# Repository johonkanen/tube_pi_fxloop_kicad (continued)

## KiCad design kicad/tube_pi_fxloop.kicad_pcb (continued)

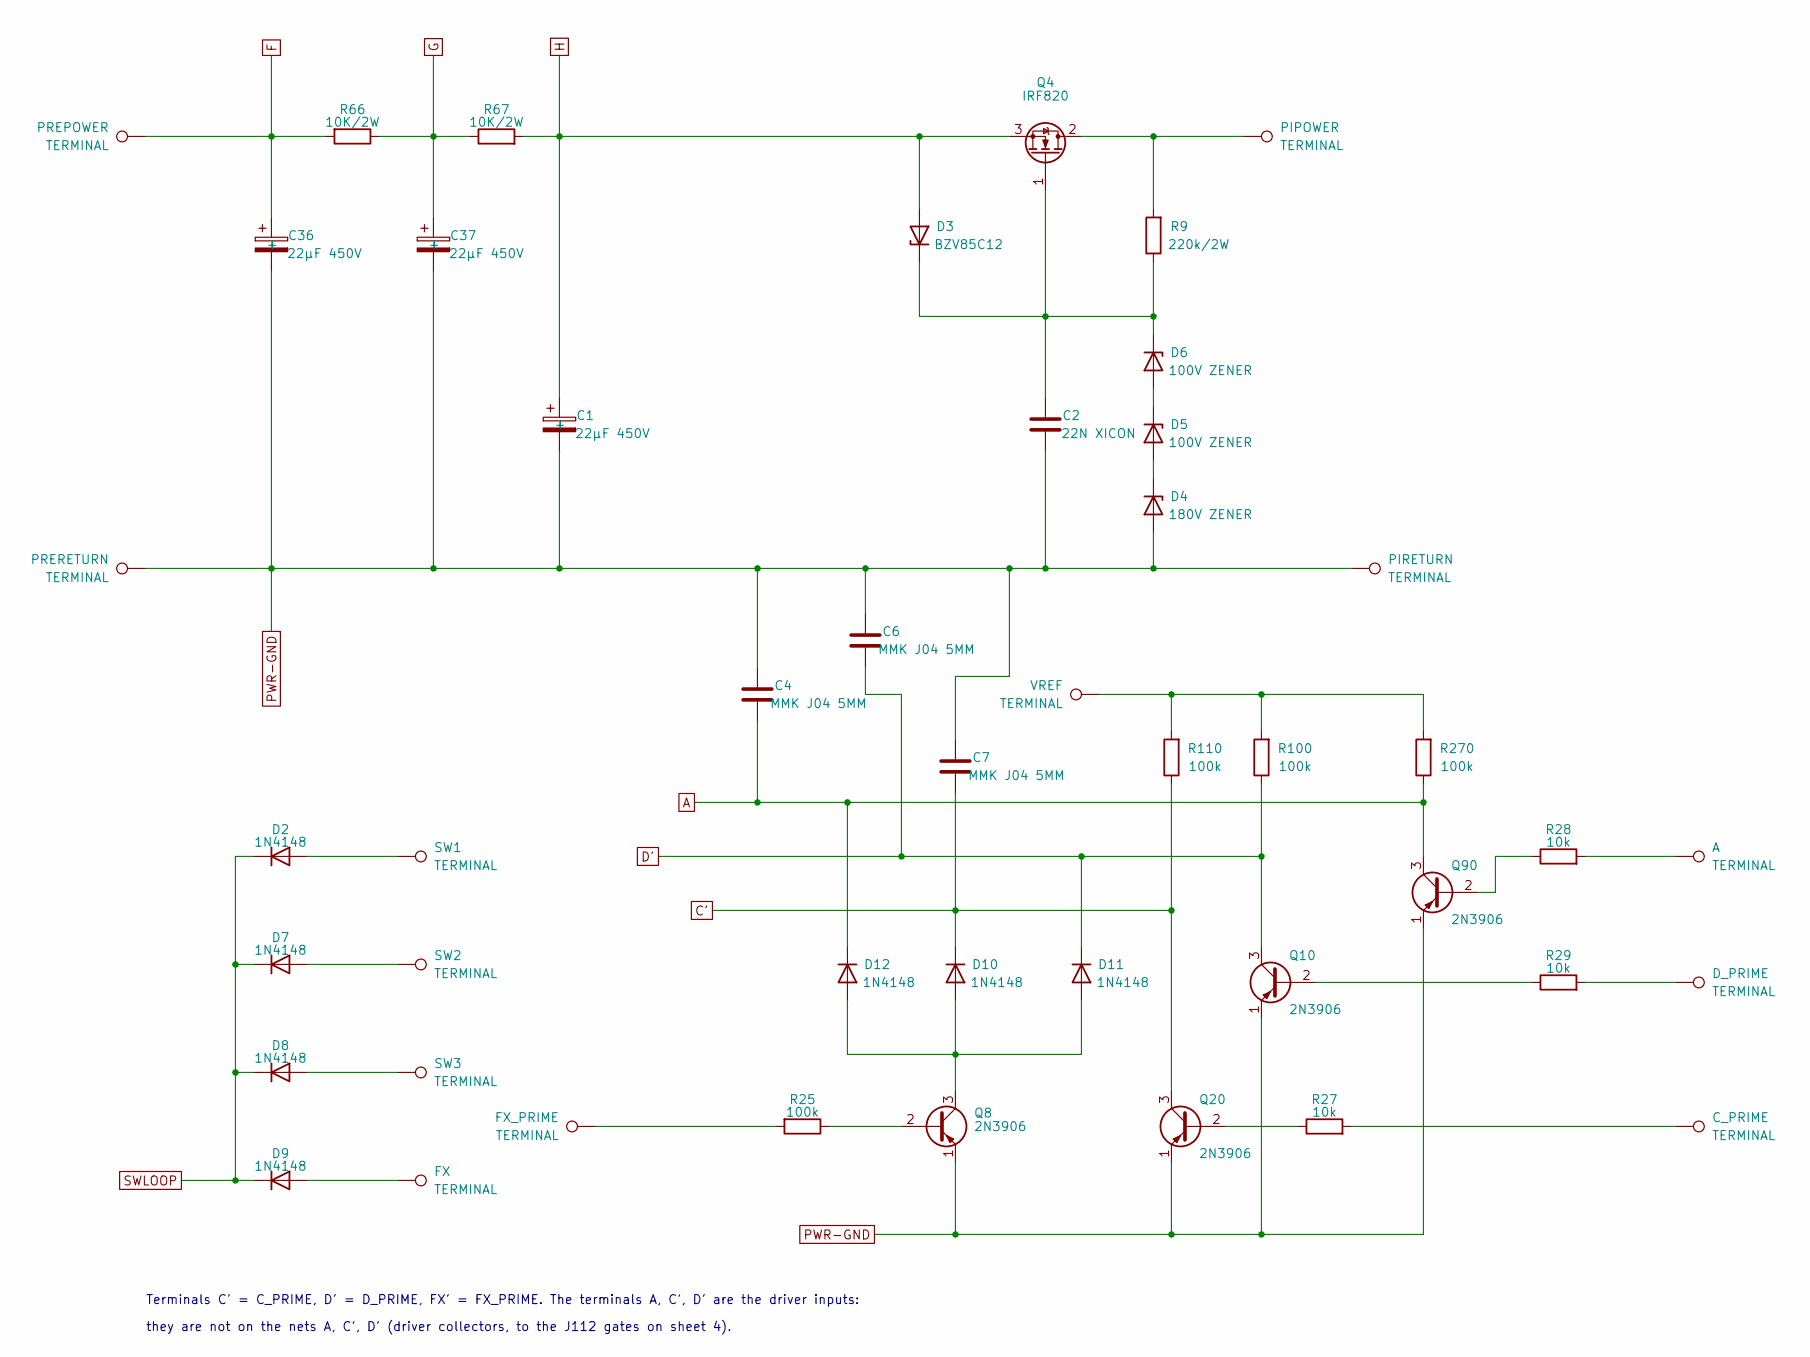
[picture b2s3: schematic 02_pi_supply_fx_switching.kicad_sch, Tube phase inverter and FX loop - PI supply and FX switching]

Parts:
A: TERMINAL; FlyLead_Pad_D3.048mm_Drill1.524mm
C1, C36, C37: 22µF 450V; CP_Radial_D16.0mm_P7.50mm_21
C2: 22N XICON; C_Rect_L13.0mm_W6.0mm_P9.70mm
C4, C6, C7: MMK J04 5MM; C_Rect_L7.2mm_W5.0mm_P5.00mm
C_PRIME: TERMINAL; FlyLead_Pad_D3.048mm_Drill1.524mm
D2, D7, D8, D9, D10, D11, D12: 1N4148; D_DO-35_SOD27_P10.16mm_Horizontal_AK
D3: BZV85C12; D_DO-41_SOD81_P10.16mm_Horizontal_AK
D4: 180V ZENER; D_DO-41_SOD81_P10.16mm_Horizontal_AK
D5, D6: 100V ZENER; D_DO-41_SOD81_P10.16mm_Horizontal_AK
D_PRIME: TERMINAL; FlyLead_Pad_D3.048mm_Drill1.524mm
FX: TERMINAL; FlyLead_Pad_D3.048mm_Drill1.524mm
FX_PRIME: TERMINAL; FlyLead_Pad_D3.048mm_Drill1.524mm
PIPOWER: TERMINAL; FlyLead_Pad_D3.048mm_Drill1.524mm
PIRETURN: TERMINAL; FlyLead_Pad_D3.048mm_Drill1.524mm
PREPOWER: TERMINAL; FlyLead_Pad_D3.048mm_Drill1.524mm
PRERETURN: TERMINAL; FlyLead_Pad_D3.048mm_Drill1.524mm
Q4: IRF820; TO-220-3_Vertical
Q8, Q10, Q20, Q90: 2N3906; TO-92_Inline_P2.03mm
R9: 220k/2W; R_Axial_DIN0414_L11.9mm_D4.5mm_P19.05mm_Horizontal
R25, R100, R110, R270: 100k; R_Axial_DIN0207_L6.3mm_D2.5mm_P10.16mm_Horizontal
R27, R28, R29: 10k; R_Axial_DIN0207_L6.3mm_D2.5mm_P10.16mm_Horizontal
R66, R67: 10K/2W; R_Axial_DIN0414_L11.9mm_D4.5mm_P19.05mm_Horizontal
SW1, SW2, SW3: TERMINAL; FlyLead_Pad_D3.048mm_Drill1.524mm
VREF: TERMINAL; FlyLead_Pad_D3.048mm_Drill1.524mm

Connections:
A: C4.2, D12.K, Q90.3 (C), R270.1; also elsewhere on the board
C': C7.2, D10.K, Q20.3 (C), R110.1; also elsewhere on the board
D': C6.2, D11.K, Q10.3 (C), R100.1; also elsewhere on the board
F: C36.2 (+), PREPOWER.1, R66.2; also elsewhere on the board
G: C37.2 (+), R66.1, R67.1; also elsewhere on the board
H: C1.2 (+), D3.A, Q4.3 (S), R67.2; also elsewhere on the board
unnamed: A.1, R28.2
unnamed: C_PRIME.1, R27.2
unnamed: D2.A, SW1.1
unnamed: D4.K, D5.A
unnamed: D5.K, D6.A
unnamed: D7.A, SW2.1
unnamed: D8.A, SW3.1
unnamed: D9.A, FX.1
unnamed: D_PRIME.1, R29.2
unnamed: FX_PRIME.1, R25.2
unnamed: PIPOWER.1, Q4.2 (D), R9.2
unnamed: C2.2, D3.K, D6.K, Q4.1 (G), R9.1
unnamed: Q8.2 (B), R25.1
unnamed: D10.A, D11.A, D12.A, Q8.3 (C)
unnamed: Q10.2 (B), R29.1
unnamed: Q20.2 (B), R27.1
unnamed: Q90.2 (B), R28.1
unnamed: R100.2, R110.2, R270.2, VREF.1
PWR-GND: C1.1 (-), C2.1, C4.1, C6.1, C7.1, C36.1 (-), C37.1 (-), D4.A, PIRETURN.1, PRERETURN.1, Q8.1 (E), Q10.1 (E), Q20.1 (E), Q90.1 (E); also elsewhere on the board
SWLOOP: D2.K, D7.K, D8.K, D9.K; also elsewhere on the board

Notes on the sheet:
Terminals C' = C_PRIME, D' = D_PRIME, FX' = FX_PRIME. The terminals A, C', D' are the driver inputs:
they are not on the nets A, C', D' (driver collectors, to the J112 gates on sheet 4).

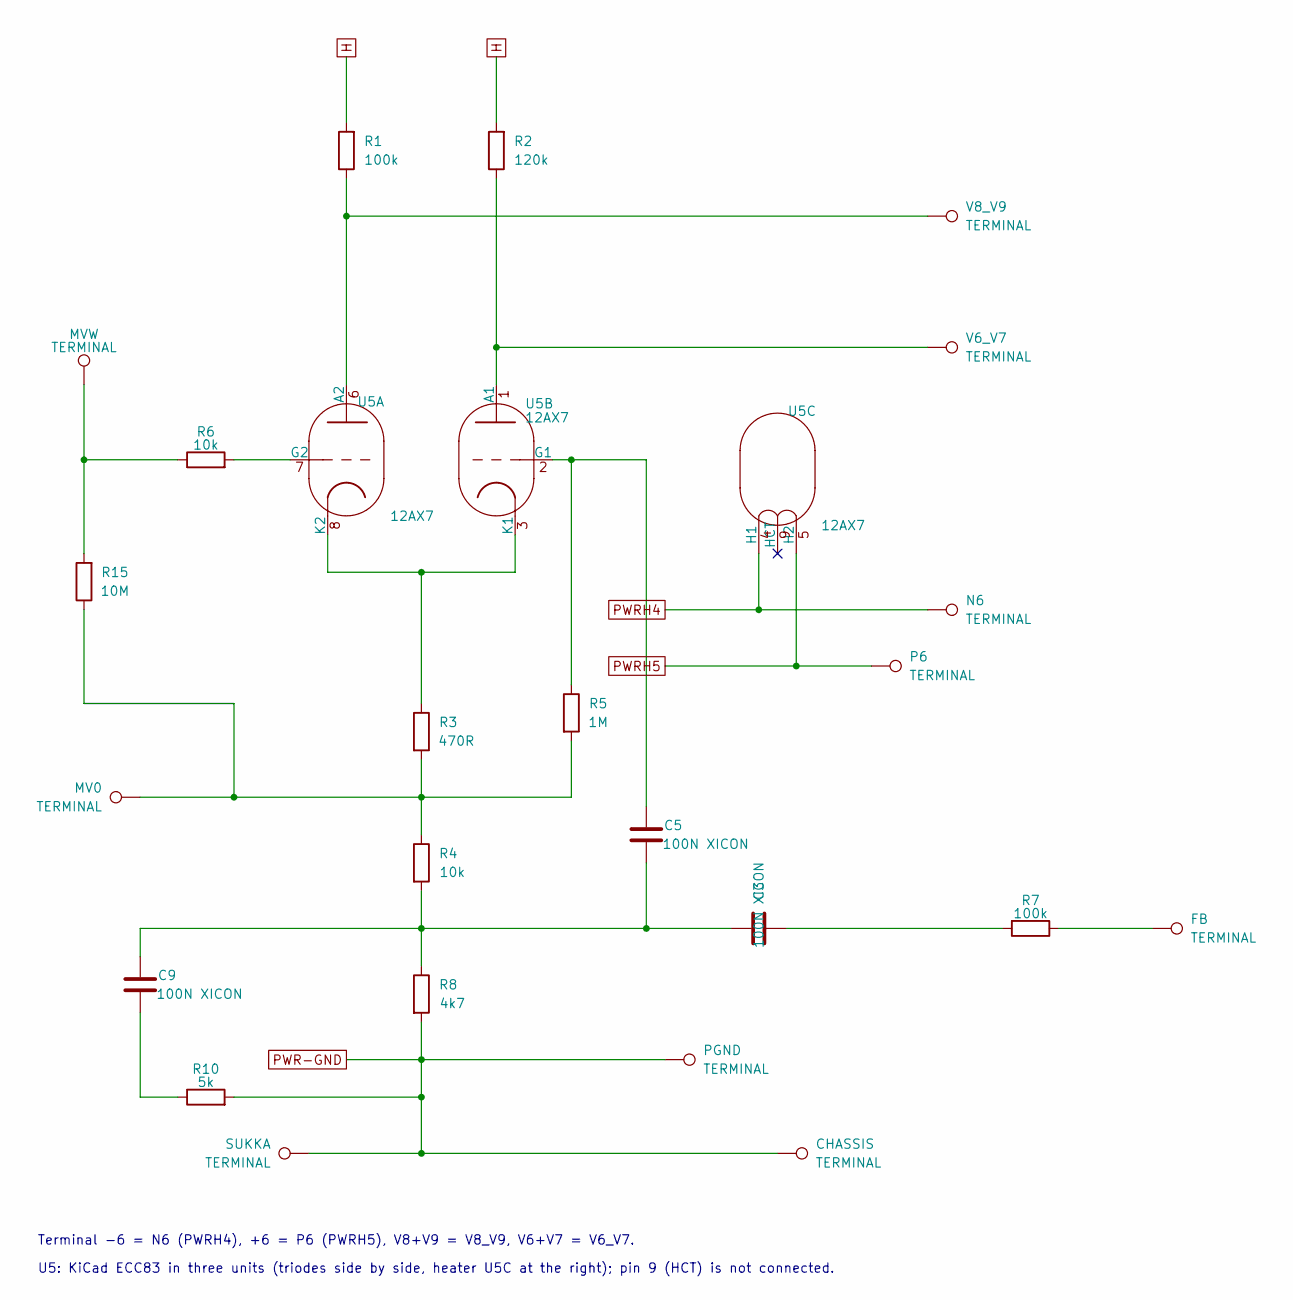
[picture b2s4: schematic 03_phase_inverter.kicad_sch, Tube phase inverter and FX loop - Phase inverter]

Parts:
C3, C5, C9: 100N XICON; C_Rect_L23.1mm_W6.0mm_P20.00mm
CHASSIS: TERMINAL; FlyLead_Pad_D3.048mm_Drill1.524mm
FB: TERMINAL; FlyLead_Pad_D3.048mm_Drill1.524mm
MV0: TERMINAL; FlyLead_Pad_D3.048mm_Drill1.524mm
MVW: TERMINAL; FlyLead_Pad_D3.048mm_Drill1.524mm
N6: TERMINAL; FlyLead_Pad_D3.048mm_Drill1.524mm
P6: TERMINAL; FlyLead_Pad_D3.048mm_Drill1.524mm
PGND: TERMINAL; FlyLead_Pad_D3.048mm_Drill1.524mm
R1: 100k; R_Axial_DIN0414_L11.9mm_D4.5mm_P19.05mm_Horizontal
R2: 120k; R_Axial_DIN0414_L11.9mm_D4.5mm_P19.05mm_Horizontal
R3: 470R; R_Axial_DIN0207_L6.3mm_D2.5mm_P10.16mm_Horizontal
R4, R6: 10k; R_Axial_DIN0207_L6.3mm_D2.5mm_P10.16mm_Horizontal
R5: 1M; R_Axial_DIN0207_L6.3mm_D2.5mm_P10.16mm_Horizontal
R7: 100k; R_Axial_DIN0207_L6.3mm_D2.5mm_P10.16mm_Horizontal
R8: 4k7; R_Axial_DIN0207_L6.3mm_D2.5mm_P10.16mm_Horizontal
R10: 5k; R_Axial_DIN0207_L6.3mm_D2.5mm_P10.16mm_Horizontal
R15: 10M; R_Axial_DIN0207_L6.3mm_D2.5mm_P10.16mm_Horizontal
SUKKA: TERMINAL; FlyLead_Pad_D3.048mm_Drill1.524mm
U5: 12AX7; Valve_Noval_Belton_PCD21.00mm
V6_V7, V8_V9: TERMINAL; FlyLead_Pad_D3.048mm_Drill1.524mm

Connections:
H: R1.2, R2.2; also elsewhere on the board
unnamed: C3.1, R7.2
unnamed: C3.2, C5.1, C9.2, R4.2, R8.1
unnamed: C9.1, R10.1
unnamed: FB.1, R7.1
unnamed: MV0.1, R3.2, R4.1, R5.2, R15.1
unnamed: MVW.1, R6.1, R15.2
unnamed: R1.1, U5.6 (A2), V8_V9.1
unnamed: R6.2, U5.7 (G2)
unnamed: R3.1, U5.3 (K1), U5.8 (K2)
unnamed: R2.1, U5.1 (A1), V6_V7.1
unnamed: C5.2, R5.1, U5.2 (G1)
PWR-GND: CHASSIS.1, PGND.1, R8.2, R10.2, SUKKA.1; also elsewhere on the board
PWRH4: N6.1, U5.4 (H1); also elsewhere on the board
PWRH5: P6.1, U5.5 (H2); also elsewhere on the board

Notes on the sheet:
Terminal -6 = N6 (PWRH4), +6 = P6 (PWRH5), V8+V9 = V8_V9, V6+V7 = V6_V7.
U5: KiCad ECC83 in three units (triodes side by side, heater U5C at the right); pin 9 (HCT) is not connected.

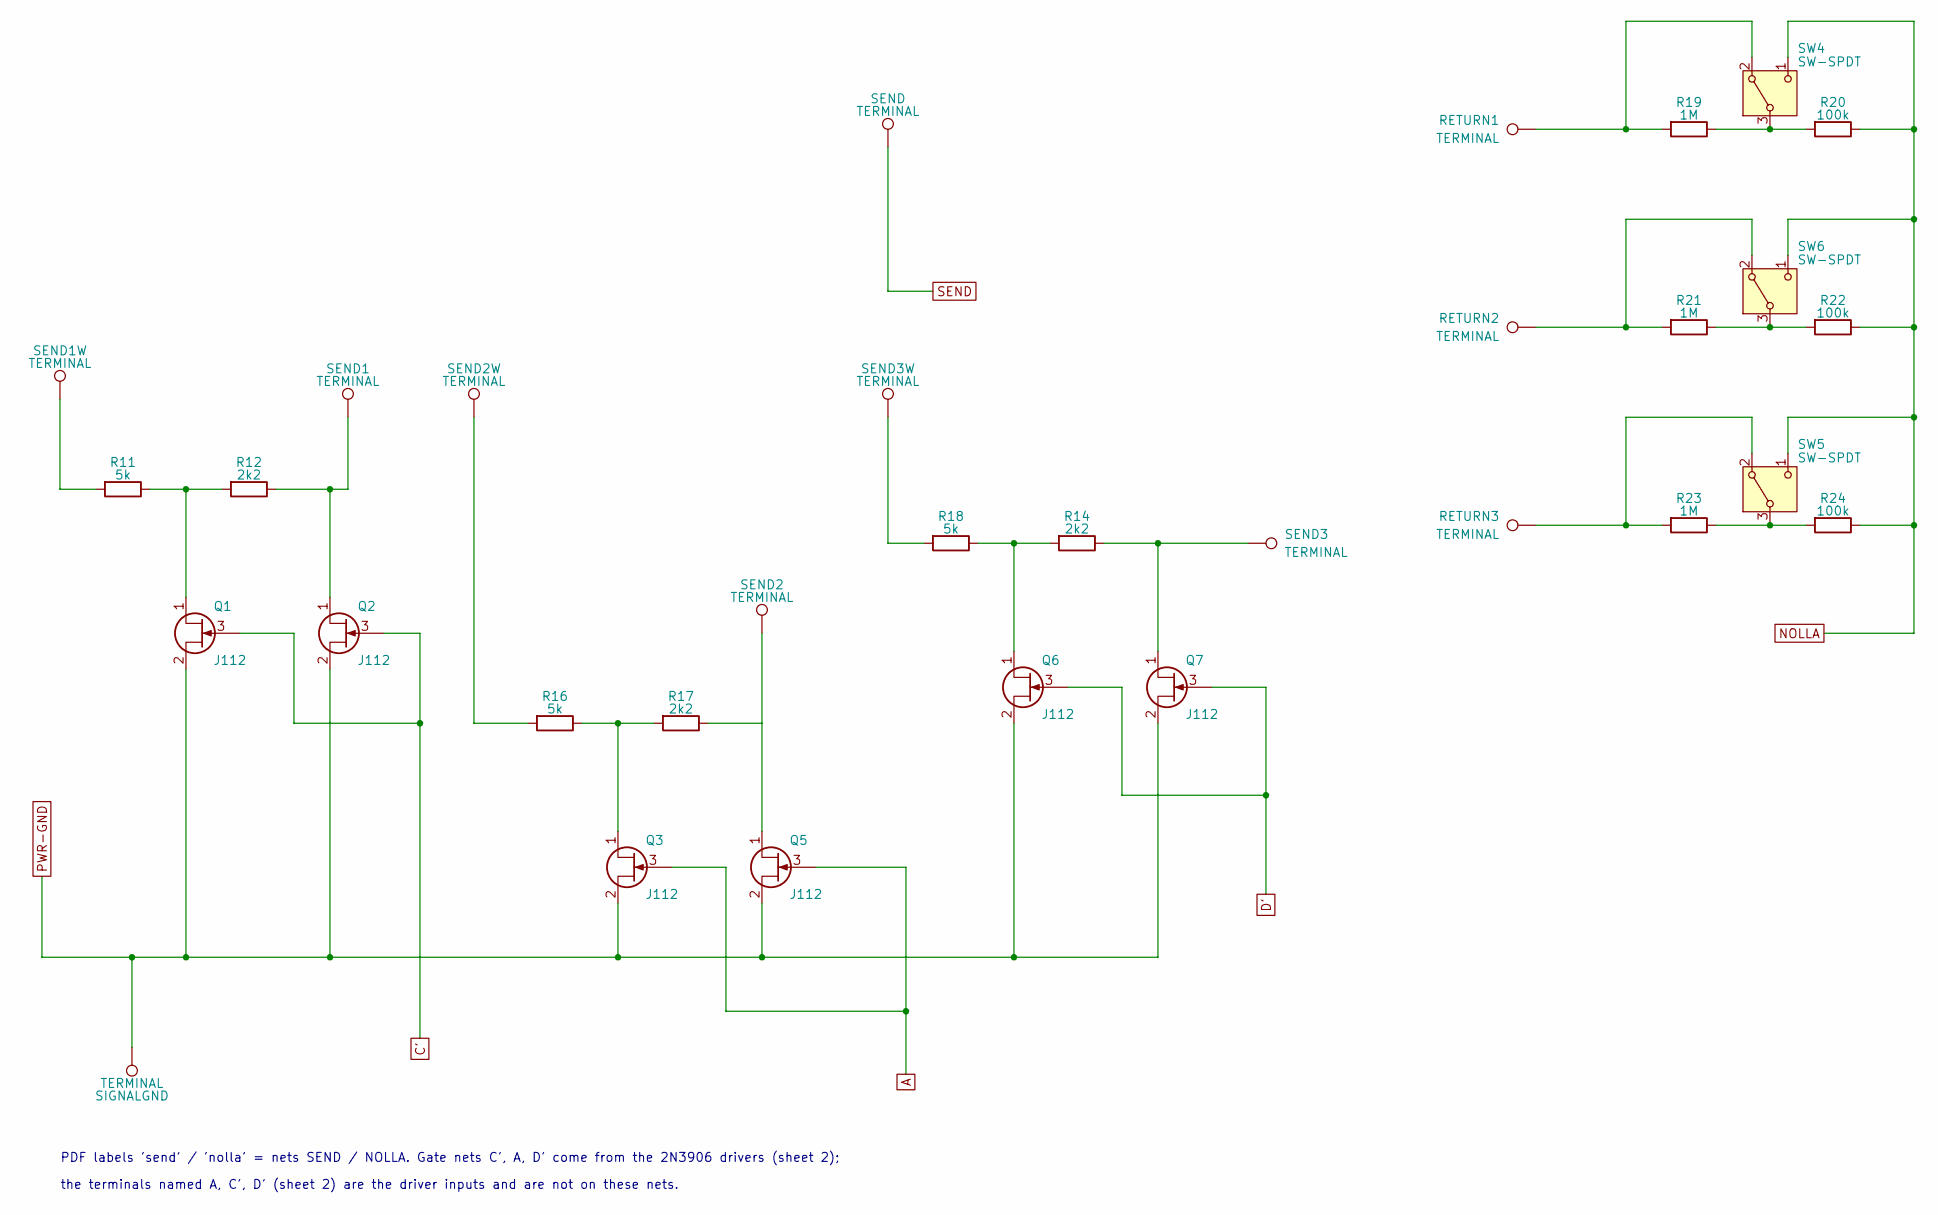
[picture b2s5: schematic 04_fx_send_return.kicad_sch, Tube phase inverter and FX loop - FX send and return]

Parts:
Q1, Q2, Q3, Q5, Q6, Q7: J112; TO-92_Inline_P2.03mm
R11, R16, R18: 5k; R_Axial_DIN0207_L6.3mm_D2.5mm_P10.16mm_Horizontal
R12, R14, R17: 2k2; R_Axial_DIN0207_L6.3mm_D2.5mm_P10.16mm_Horizontal
R19, R21, R23: 1M; R_Axial_DIN0207_L6.3mm_D2.5mm_P10.16mm_Horizontal
R20, R22, R24: 100k; R_Axial_DIN0207_L6.3mm_D2.5mm_P10.16mm_Horizontal
RETURN1, RETURN2, RETURN3: TERMINAL; FlyLead_Pad_D3.048mm_Drill1.524mm
SEND, SEND1, SEND1W, SEND2, SEND2W, SEND3, SEND3W: TERMINAL; FlyLead_Pad_D3.048mm_Drill1.524mm
SIGNALGND: TERMINAL; FlyLead_Pad_D3.048mm_Drill1.524mm
SW4, SW5, SW6: SW-SPDT; SW_SPDT_3Holes_Proteus

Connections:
A: Q3.3 (G), Q5.3 (G); also elsewhere on the board
C': Q1.3 (G), Q2.3 (G); also elsewhere on the board
D': Q6.3 (G), Q7.3 (G); also elsewhere on the board
NOLLA: R20.1, R22.1, R24.1, SW4.1 (NO), SW5.1 (NO), SW6.1 (NO); also elsewhere on the board
unnamed: Q1.1 (D), R11.1, R12.2
unnamed: Q2.1 (D), R12.1, SEND1.1
unnamed: Q3.1 (D), R16.1, R17.2
unnamed: Q5.1 (D), R17.1, SEND2.1
unnamed: Q6.1 (D), R14.2, R18.1
unnamed: Q7.1 (D), R14.1, SEND3.1
unnamed: R11.2, SEND1W.1
unnamed: R16.2, SEND2W.1
unnamed: R18.2, SEND3W.1
unnamed: R19.1, R20.2, SW4.3 (COM)
unnamed: R19.2, RETURN1.1, SW4.2 (NC)
unnamed: R23.1, R24.2, SW5.3 (COM)
unnamed: R23.2, RETURN3.1, SW5.2 (NC)
unnamed: R21.1, R22.2, SW6.3 (COM)
unnamed: R21.2, RETURN2.1, SW6.2 (NC)
PWR-GND: Q1.2 (S), Q2.2 (S), Q3.2 (S), Q5.2 (S), Q6.2 (S), Q7.2 (S), SIGNALGND.1; also elsewhere on the board
SEND: SEND.1; also elsewhere on the board

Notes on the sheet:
PDF labels 'send' / 'nolla' = nets SEND / NOLLA. Gate nets C', A, D' come from the 2N3906 drivers (sheet 2);
the terminals named A, C', D' (sheet 2) are the driver inputs and are not on these nets.

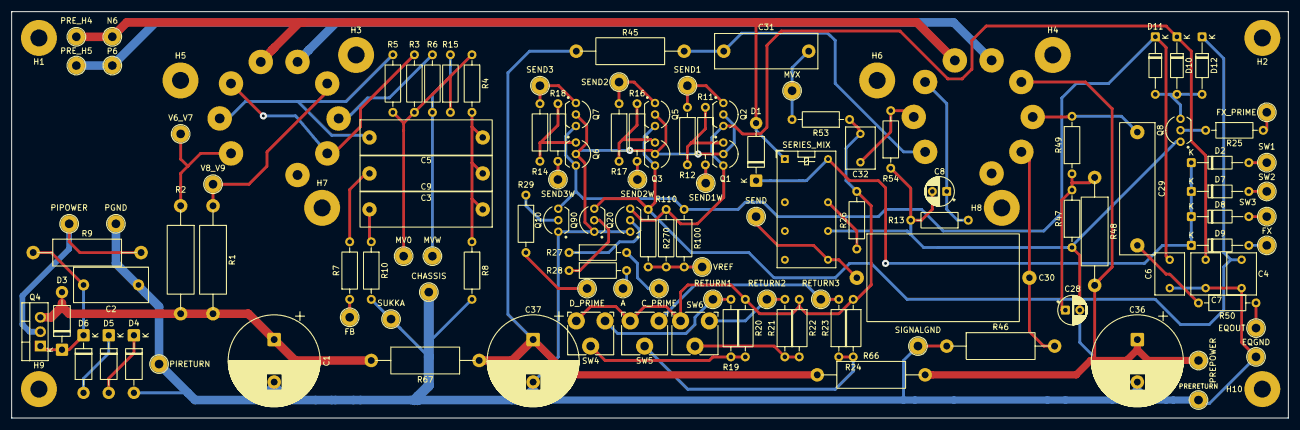
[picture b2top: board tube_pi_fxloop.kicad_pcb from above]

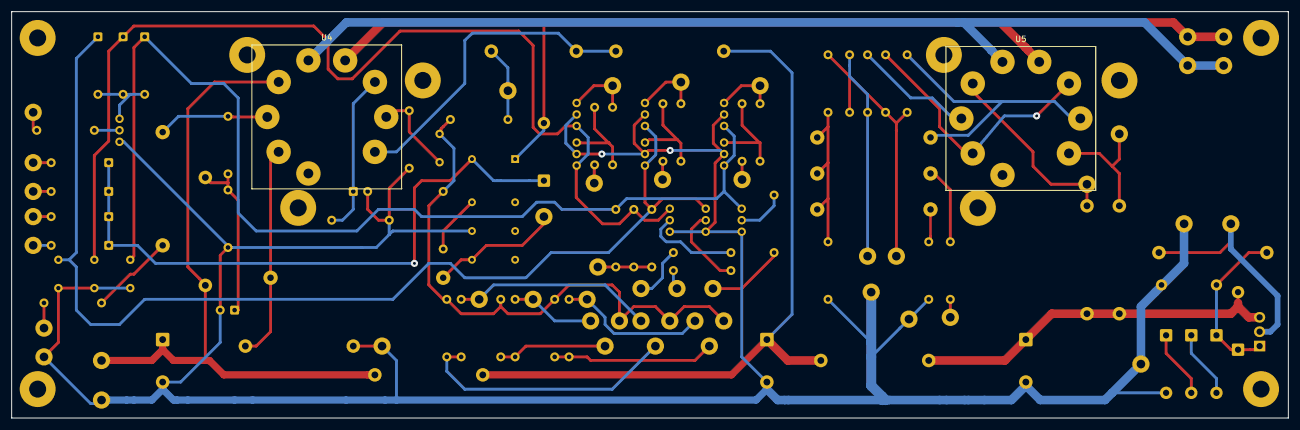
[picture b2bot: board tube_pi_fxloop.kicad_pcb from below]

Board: 2 copper layers, 225.4 x 71.8 mm, 136 parts (2 on the bottom side), 66 nets.

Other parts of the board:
H1, H2, H3, H4, H5, H6, H7, H8, H9, H10: MountingHole_3.0mm; MountingHole_3.0mm_PTH_Pad6.35mm

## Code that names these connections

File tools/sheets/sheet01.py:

#!/usr/bin/env python3
"""Sheet 1 - FX loop driver (PDF page 1): U4 12AT7. Triode 1 (pins 1-3) is the gain stage (anode
load R45 from G, grid from NOLLA via C32, cathode HYPPY2 with R13 / C8), its output goes via C31 to
MVX and R53; triode 2 (pins 6-8) is the cathode follower on F (grid bias R47-R49 / C28, input EQOUT
via R50 / C29) driving SEND through C30. Relay SERIES/MIX connects R26 (to NOLLA) to ground or SEND.

Differences to the PDF drawing (same nets): the two triodes of KiCad's ECC83 symbol are drawn side
by side and the heater unit below them; the relay is one symbol with both poles and the coil (the
unused pole 2 carries no-connect flags), turned so that the common contact faces R26."""
from _common import *  # noqa: F401,F403

sh = sheet("01_fx_loop_driver.kicad_sch")

XA, XB, YG = 95, 111, 49    # anode columns of pin 6 / pin 1, grid row
GND = 113                   # PWR-GND row
u1, u2, u3 = noval(sh, "U4", P(XA, YG), P(XB, YG), P(103, 68), mirror_b=True)

# triode 2 (6, 7, 8): anode on F, grid bias, EQOUT input
sh.glabel("F", *P(XA, 20), 90)
sh.wire(P(XA, 20), u1.pin(6))
r48t, r48b = pv(sh, "R48", 73, 40, top=2)
sh.wire(r48t, P(73, 31), P(XA, 31))
sh.junction(*P(XA, 31))
term(sh, "EQOUT", *P(25, YG), "left")
r50l, r50r = ph(sh, "R50", 34, YG, left=2)
c29l, c29r = ph(sh, "C29", 47, YG, left=1)
sh.wire(P(25, YG), r50l)
sh.wire(r50r, c29l)
sh.wire(c29r, u1.pin(7))
r49t, r49b = pv(sh, "R49", 63, 62, top=2)
sh.wire(P(63, YG), r49t)
c28t, c28b = pv(sh, "C28", 63, 88, top="+")
sh.wire(r49b, c28t)
r47t, r47b = pv(sh, "R47", 73, 88, top=2)
sh.wire(r48b, r47t)
sh.wire(P(63, 71), P(73, 71))
junctions(sh, P(63, YG), P(63, 71), P(73, 71))
sh.wire(c28b, P(63, GND))
sh.wire(r47b, P(73, GND))

# cathode 8: R46 to ground, C30 to SEND
sh.wire(u1.pin(8), P(93, 59), P(85, 59), P(85, 98))
r46t, r46b = pv(sh, "R46", 85, 104, top=2)
sh.wire(P(85, 98), r46t)
sh.wire(r46b, P(85, GND))
c30l, c30r = ph(sh, "C30", 99, 98, left=1)
sh.wire(P(85, 98), c30l)
sh.junction(*P(85, 98))

# triode 1 (1, 2, 3): anode load from G, C31 to MVX / R53, grid from NOLLA via C32, R54
sh.glabel("G", *P(XB, 20), 90)
r45t, r45b = pv(sh, "R45", XB, 28, top=2)
sh.wire(P(XB, 20), r45t)
sh.wire(r45b, u2.pin(1))
c31l, c31r = ph(sh, "C31", 125, 39, left=1)
sh.wire(P(XB, 39), c31l)
sh.junction(*P(XB, 39))
XR = 171                    # column of MVX, R53, R26 and the relay's common contact
term(sh, "MVX", *P(XR, 29), "up")
r53t, r53b = pv(sh, "R53", XR, 52, top=2)
sh.wire(P(XR, 29), r53t)
sh.wire(c31r, P(XR, 39))
sh.junction(*P(XR, 39))
r26t, r26b = pv(sh, "R26", XR, 72, top=2)
sh.wire(r53b, r26t)
sh.wire(P(XR, 61), P(179, 61))
sh.glabel("NOLLA", *P(179, 61), 0)
c32l, c32r = ph(sh, "C32", 145, YG, left=1)
sh.wire(u2.pin(2), c32l)
sh.wire(c32r, P(161, YG), P(161, 61), P(XR, 61))
sh.junction(*P(XR, 61))
r54t, r54b = pv(sh, "R54", 137, 66, top=2)
sh.wire(P(137, YG), r54t)
sh.junction(*P(137, YG))
sh.wire(r54b, P(137, GND))

# cathode 3 = HYPPY2 (local label, twice as in the PDF), R13 / C8 to ground
sh.wire(u2.pin(3), P(113, 59), P(121, 59))
sh.label("HYPPY2", *P(121, 59), 0)
c8t, c8b = pv(sh, "C8", 121, 124, top="-")
r13t, r13b = pv(sh, "R13", 133, 124, top=2)
sh.wire(c8t, P(121, GND))
sh.wire(r13t, P(133, GND))
sh.wire(c8b, P(121, 137), P(141, 137))
sh.wire(r13b, P(133, 137))
sh.junction(*P(133, 137))
sh.label("HYPPY2", *P(141, 137), 0)

# relay SERIES/MIX (rotated 180: common 2 on top, contacts 1 / 3 below, coil 4 / 5 on the right)
k = sh.place(sym("SERIES_MIX"), "SERIES_MIX", *P(XR, 88), 180, value=sh_value("SERIES_MIX"),
             ref_at=(P(150, 0)[0], P(0, 86)[1], 0, "right"), value_at=(P(150, 0)[0], P(0, 88)[1], 0, "right"))
sh.wire(r26b, k.pin(2))
sh.wire(c30r, P(169, 98), k.pin(1))
sh.wire(k.pin(3), P(173, GND))
for n in "678":
    sh.no_connect(*k.pin(n))
d1a, d1k = pv(sh, "D1", 187, 88, top="A")
sh.wire(k.pin(5), P(179, 80), P(193, 80))
sh.wire(P(187, 80), d1a)
sh.glabel("PWRH4", *P(193, 80), 0)
sh.wire(k.pin(4), P(179, 96), P(193, 96))
sh.wire(d1k, P(187, 96))
sh.glabel("SWLOOP", *P(193, 96), 0)
junctions(sh, P(187, 80), P(187, 96))
sh.wire(P(115, 98), P(115, 104))
sh.junction(*P(115, 98))
sh.glabel("SEND", *P(115, 104), 270)

# ground row
term(sh, "EQGND", *P(45, GND), "left")
sh.wire(P(45, GND), P(173, GND))
sh.wire(P(85, GND), P(85, 120))
sh.glabel("PWR-GND", *P(85, 120), 270)
junctions(sh, P(63, GND), P(73, GND), P(85, GND), P(121, GND), P(133, GND), P(137, GND))

# heaters
for net, pin, y, ref in (("PWRH4", u3.pin(4), 81, "PRE_H4"), ("PWRH5", u3.pin(5), 87, "PRE_H5")):
    yy = P(0, y)[1]
    sh.glabel(net, *P(95, y), 180)
    term(sh, ref, *P(119, y), "right")
    sh.wire(P(95, y), P(119, y))
    sh.wire(pin, (pin[0], yy))
    sh.junction(pin[0], yy)

sh.text("R47 = 50-100k (Proteus hand note; value 33k)", *P(45, 122))
sh.text("PDF labels 'send' / 'nolla' = nets SEND / NOLLA (Proteus net names are case-insensitive).", *P(45, 145))
sh.text("Terminals PRE-H4 / PRE-H5 = PRE_H4 / PRE_H5; relay SERIES/MIX = SERIES_MIX (pins 6-8, pole 2: not connected).", *P(45, 148))
sh.text("U4: KiCad ECC83 symbol in three units (heater U4C below); pin 9 (HCT) is not connected. Value 12AT7.", *P(45, 151))
sh.save()
print("sheet01: written")

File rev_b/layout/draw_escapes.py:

#!/usr/bin/env python3
"""Scripted escapes where the router boxes itself in: kipy draw_escapes.py IN OUT

The MCP23S17's GPA0-GPA2 (pins 21-23: FX_DRY, FX_WET, FX_UNMUTE) sit in the middle of its west row,
facing the ULN2803A 3 mm away; every routing order left one of them without an exit. Each gets a short
stub west and a via (0.6 / 0.3 mm), staggered (pin 22's via one step further out, its stub passing
between the other two), so the router continues from the vias on the inner layers. Locked.
"""
import os
import sys

import pcbnew

sys.path.insert(0, os.path.dirname(os.path.abspath(__file__)))
import placement as P  # noqa: E402

ESC = {"21": 1.85, "22": 2.85, "23": 1.85}     # via distance west of the pad centre (chassis mm)


def mm(v):
    return pcbnew.FromMM(v)


def main():
    b = pcbnew.LoadBoard(sys.argv[1])
    u = {f.GetReference(): f for f in b.GetFootprints()}["U401"]
    for num, dx in ESC.items():
        p = u.FindPadByNumber(num)
        x, y = P.to_chassis(pcbnew.ToMM(p.GetPosition().x), pcbnew.ToMM(p.GetPosition().y))
        vx, vy = P.to_board(x - dx, y)
        t = pcbnew.PCB_TRACK(b)
        t.SetStart(p.GetPosition()); t.SetEnd(pcbnew.VECTOR2I(mm(vx), mm(vy)))
        t.SetWidth(mm(0.2)); t.SetLayer(pcbnew.F_Cu); t.SetNet(p.GetNet()); t.SetLocked(True); b.Add(t)
        v = pcbnew.PCB_VIA(b)
        v.SetPosition(pcbnew.VECTOR2I(mm(vx), mm(vy))); v.SetWidth(mm(0.6)); v.SetDrill(mm(0.3))
        v.SetNet(p.GetNet()); v.SetLocked(True); b.Add(v)
    b.Save(sys.argv[2])
    print("expander GPA0-GPA2 escapes drawn")


if __name__ == "__main__":
    main()
